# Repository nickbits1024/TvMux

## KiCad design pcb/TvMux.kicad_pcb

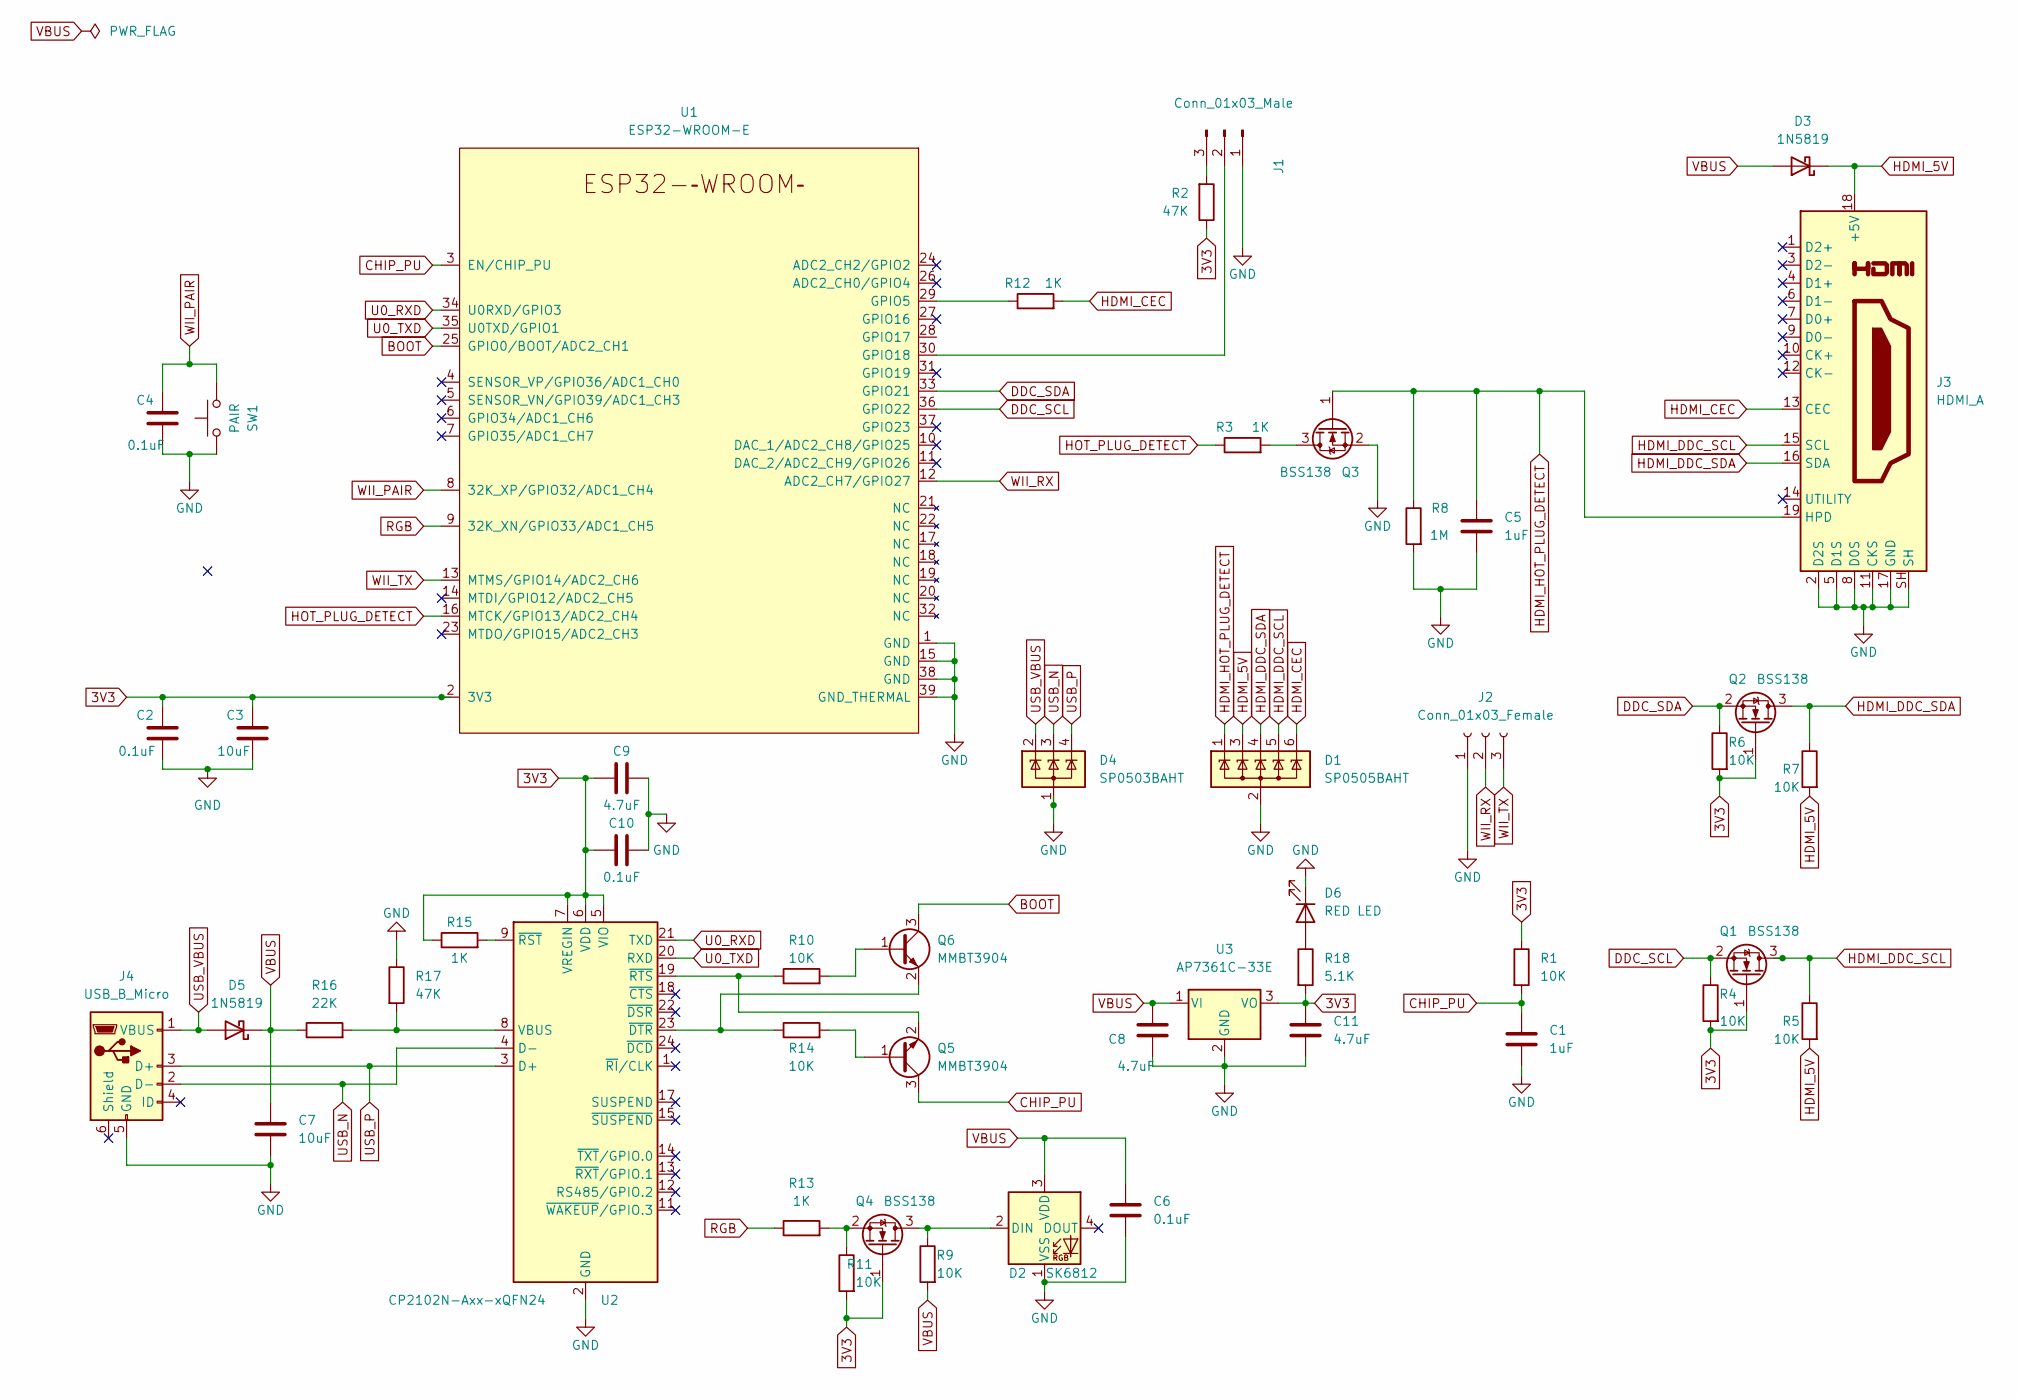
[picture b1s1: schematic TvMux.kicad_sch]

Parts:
C1, C5: 1uF; C_0603_1608Metric
C2, C4, C6, C10: 0.1uF; C_0603_1608Metric
C3, C7: 10uF; C_0603_1608Metric
C8, C9, C11: 4.7uF; C_0603_1608Metric
D1: SP0505BAHT; SOT-23-6
D2: SK6812; LED_SK6812_PLCC4_5.0x5.0mm_P3.2mm
D3, D5: 1N5819; D_SOD-323
D4: SP0503BAHT; SOT-143
D6: RED LED; LED_0603_1608Metric
J1: Conn_01x03_Male; PinHeader_1x03_P2.54mm_Vertical
J2: Conn_01x03_Female; JST_XH_B3B-XH-A_1x03_P2.50mm_Vertical
J3: HDMI_A; 2086581051
J4: USB_B_Micro; USB_Micro-B_Molex-105017-0001
Q1, Q2, Q3, Q4: BSS138; SOT-323_SC-70
Q5, Q6: MMBT3904; SOT-23
R1, R4, R5, R6, R7, R9, R10, R11, R14: 10K; R_0603_1608Metric
R2, R17: 47K; R_0603_1608Metric
R3, R12, R13, R15: 1K; R_0603_1608Metric
R8: 1M; R_0603_1608Metric
R16: 22K; R_0603_1608Metric
R18: 5.1K; R_0603_1608Metric
SW1: PAIR; SW_Push_1P1T_NO_6x6mm_H9.5mm
U1: ESP32-WROOM-E; ESP32-WROOM-32E
U2: CP2102N-Axx-xQFN24; QFN-24-1EP_4x4mm_P0.5mm_EP2.6x2.6mm
U3: AP7361C-33E; SOT-223-3_TabPin2

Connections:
3V3: C2.1, C3.1, C9.1, C10.1, C11.2, Q1.1 (G), Q2.1 (G), Q4.1 (G), R1.1, R2.1, R4.2, R6.2, R11.2, R15.1, R18.2, U1.2 (3V3), U2.5 (VIO), U2.6 (VDD), U2.7 (VREGIN), U3.3 (VO)
BOOT: Q6.3 (C), U1.25 (GPIO0/BOOT/ADC2_CH1)
CHIP_PU: C1.1, Q5.3 (C), R1.2, U1.3 (EN/CHIP_PU)
DDC_SCL: Q1.2 (S), R4.1, U1.36 (GPIO22)
DDC_SDA: Q2.2 (S), R6.1, U1.33 (GPIO21)
GND: C1.2, C2.2, C3.2, C4.2, C5.1, C6.1, C7.2, C8.1, C9.2, C10.2, C11.1, D1.2 (A), D2.1 (VSS), D4.1 (A), D6.1 (K), J1.1, J2.1, J3.2 (D2S), J3.5 (D1S), J3.8 (D0S), J3.11 (CKS), J3.17 (GND), J3.SH, J4.5 (GND), Q3.2 (S), R8.2, R17.1, SW1.1, U1.1 (GND), U1.15 (GND), U1.38 (GND), U1.39 (GND_THERMAL), U2.2 (GND), U2.25 (GND), U3.2 (GND)
HDMI_5V: D1.3 (K), D3.1 (K), J3.18 (+5V), R5.2, R7.2
HDMI_CEC: D1.6 (K), J3.13 (CEC), R12.2
HDMI_DDC_SCL: D1.5 (K), J3.15 (SCL), Q1.3 (D), R5.1
HDMI_DDC_SDA: D1.4 (K), J3.16 (SDA), Q2.3 (D), R7.1
HDMI_HOT_PLUG_DETECT: C5.2, D1.1 (K), J3.19 (HPD), Q3.1 (G), R8.1
HOT_PLUG_DETECT: R3.1, U1.16 (MTCK/GPIO13/ADC2_CH4)
unnamed: D2.2 (DIN), Q4.3 (D), R9.1
unnamed: D6.2 (A), R18.1
unnamed: J1.2, U1.30 (GPIO18)
unnamed: J1.3, R2.2
unnamed: Q3.3 (D), R3.2
unnamed: Q4.2 (S), R11.1, R13.2
unnamed: Q5.1 (B), R14.2
unnamed: Q5.2 (E), R10.1, U2.19 (~RTS)
unnamed: Q6.1 (B), R10.2
unnamed: Q6.2 (E), R14.1, U2.23 (~DTR)
unnamed: R12.1, U1.29 (GPIO5)
unnamed: R16.2, R17.2, U2.8 (VBUS)
unnamed: R15.2, U2.9 (~RST)
RGB: R13.1, U1.9 (32K_XN/GPIO33/ADC1_CH5)
U0_RXD: U1.34 (U0RXD/GPIO3), U2.21 (TXD)
U0_TXD: U1.35 (U0TXD/GPIO1), U2.20 (RXD)
USB_N: D4.3 (K), J4.2 (D-), U2.4 (D-)
USB_P: D4.4 (K), J4.3 (D+), U2.3 (D+)
USB_VBUS: D4.2 (K), D5.2 (A), J4.1 (VBUS)
VBUS: C6.2, C7.1, C8.2, D2.3 (VDD), D3.2 (A), D5.1 (K), R9.2, R16.1, U3.1 (VI)
WII_PAIR: C4.1, SW1.2, U1.8 (32K_XP/GPIO32/ADC1_CH4)
WII_RX: J2.2, U1.12 (ADC2_CH7/GPIO27)
WII_TX: J2.3, U1.13 (MTMS/GPIO14/ADC2_CH6)

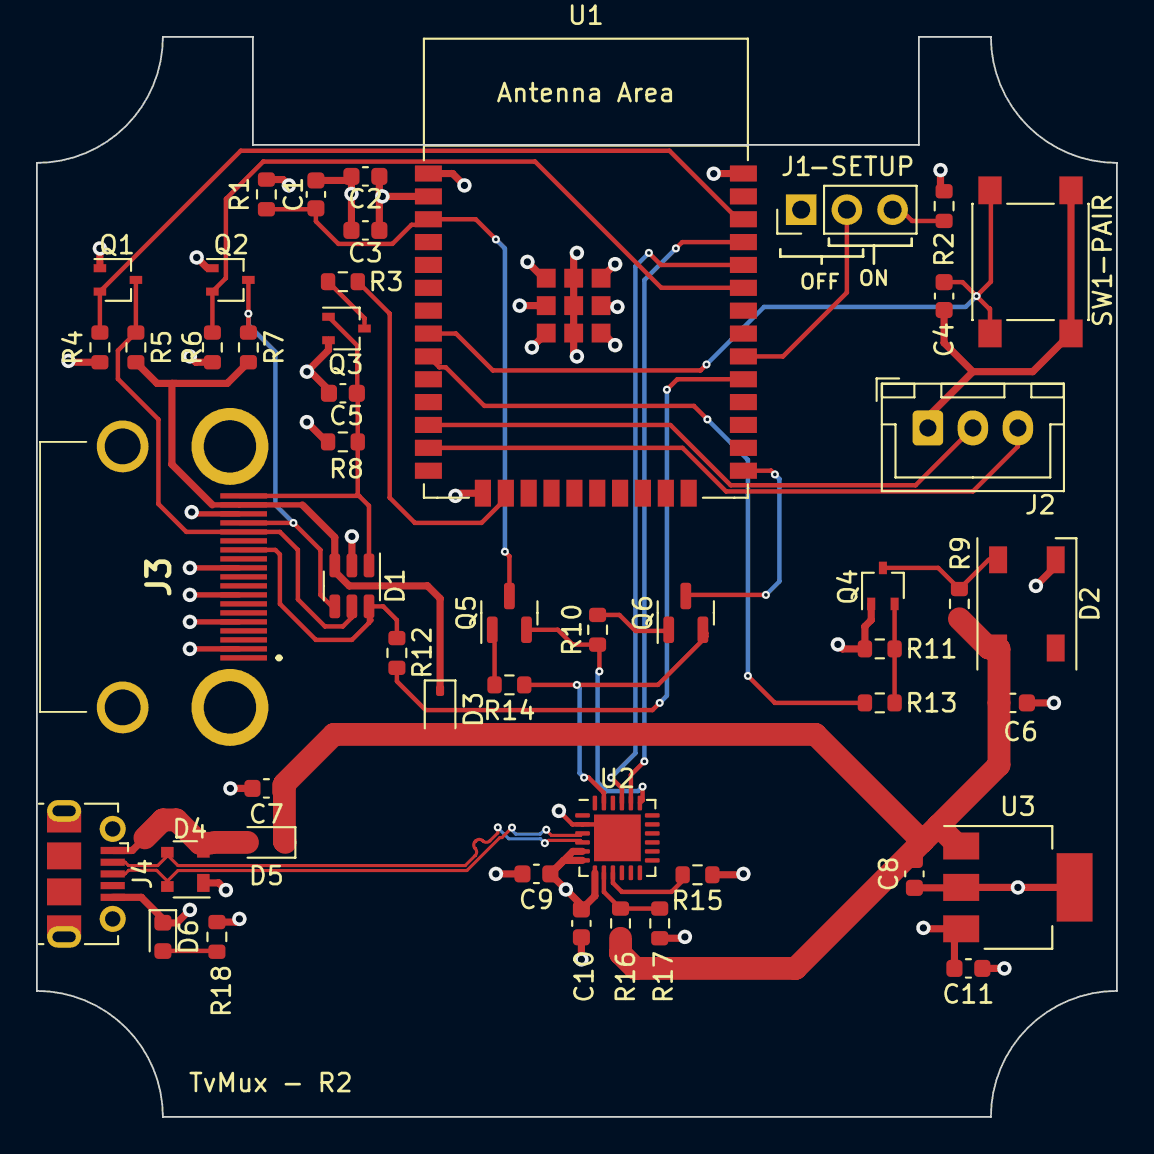
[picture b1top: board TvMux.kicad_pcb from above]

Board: 4 copper layers, 60.0 x 60.0 mm, 49 parts (0 on the bottom side), 35 nets.

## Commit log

2021-06-09 first
2021-06-09 monitor speed
2021-06-12 edid
2021-06-12 fix led
2021-06-13 edid parsing, hotplug
2021-06-13 fix xmit
2021-06-13 remove audio
2021-06-13 warnings and response fix
2021-06-13 tweaks
2021-06-14 reply
2021-06-14 remove dbg
2021-06-14 cleanup
2021-06-17 reorg
2021-06-20 fix semaphores
2021-06-26 two pins
2021-07-30 wii api
2021-07-30 tweak wii timing
2021-07-31 wii tweaks
2021-07-31 pairing api!
2021-08-01 tv/wii cec api
2021-08-01 remove mux
2021-08-03 tv on/off remove impersonation
2021-08-03 play/pause address filter
2021-08-03 response mux
2021-08-03 bugs
2021-08-04 retry wip
2021-08-08 retries wip
2021-08-12 replace async web server
2021-08-29 change cec type
2021-08-29 tweak pair
2022-08-12 fix hdmi input
2022-10-27 udpates
2022-10-31 steam
2022-11-03 updated steam support
2022-11-03 remove unncessary check
2022-11-05 tweak steam ping/timing
2022-12-23 steam tweaks
2022-12-24 fix incorrect stealing logic steam timing tweaks
2022-12-24 change stealing logging msg
2022-12-30 new steam APIs
2023-01-09 async post, pending statuses
2023-01-25 rtx 4090 ordering
2023-01-25 steam_power_on tweak
2023-03-19 fix open
2023-03-19 dec max retry
2023-04-02 pcb WIP
2023-04-08 PCB R1
2023-05-18 esp idf wip
2023-05-26 idf compiles
2023-05-27 working idf version
2023-05-28 wii fixes cec loop reorg
2023-05-29 tv timing tweaks 1 mem leak 1 semaphore leak
2023-06-01 1 cec gpio retry tweaks led colors
2023-06-01 power state handling
2023-06-01 wii led colors
2023-06-03 cec tweaks logging output
2023-06-03 pcb updates
2023-06-04 c++ gone
2023-06-07 cec start working
2023-06-11 almost working tx/tx needs responding to ack
2023-06-12 tx/rx working w/ ack!
2023-06-12 timing tweaks error handling
2023-06-14 small tweaks
2023-06-14 fix ack bug when sending to self
2023-06-22 feature complete, untested
2023-06-26 cec power status cec log tv active source
2023-06-29 steam fixes
2023-06-30 steam tweaks & logging
2023-06-30 post_json topology
2023-07-09 remove cache
2023-07-09 fix setup mode hotplug
2023-07-15 click commmand queue delay tv home menu before power off
2024-05-12 debug tweaks
2024-10-12 fix ping bug
